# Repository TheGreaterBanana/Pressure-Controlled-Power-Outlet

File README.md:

# Pressure-Controlled-Power-Outlet
This is my (for sure) late Birthday present for my mom:

The idea for this project is that she have a water bin that holds water off of the roof of her house. Which my mother uses to water her gardens. The problem is that the pump she uses does not stop when the pressure starts to build!

So this is ment to fix this by using a water pressure sensor to see when the hose nozzel is closed by detecting a large jump in pressure then disablling the outlet that is powering the pump. Then when the nozzel is opened again this will detect the drop in pressure and re-enable the outlet.

This respository will have the code for the pico (RP2040) microcontroller, the schematics for the PCB and the case that will be used. 

The design philosophy for this project is to have everything as simple and cheap as possible, for this as many components as possible will be through hole as I dont want to pay to have parts placed on the pcb. If a part has to be surface mount it will have a extra large footprint to make it as easy as possible to assemble.

The specs:
    - 125V
    - 20A
    - GFCI protected outlets
    - Useable outdoors

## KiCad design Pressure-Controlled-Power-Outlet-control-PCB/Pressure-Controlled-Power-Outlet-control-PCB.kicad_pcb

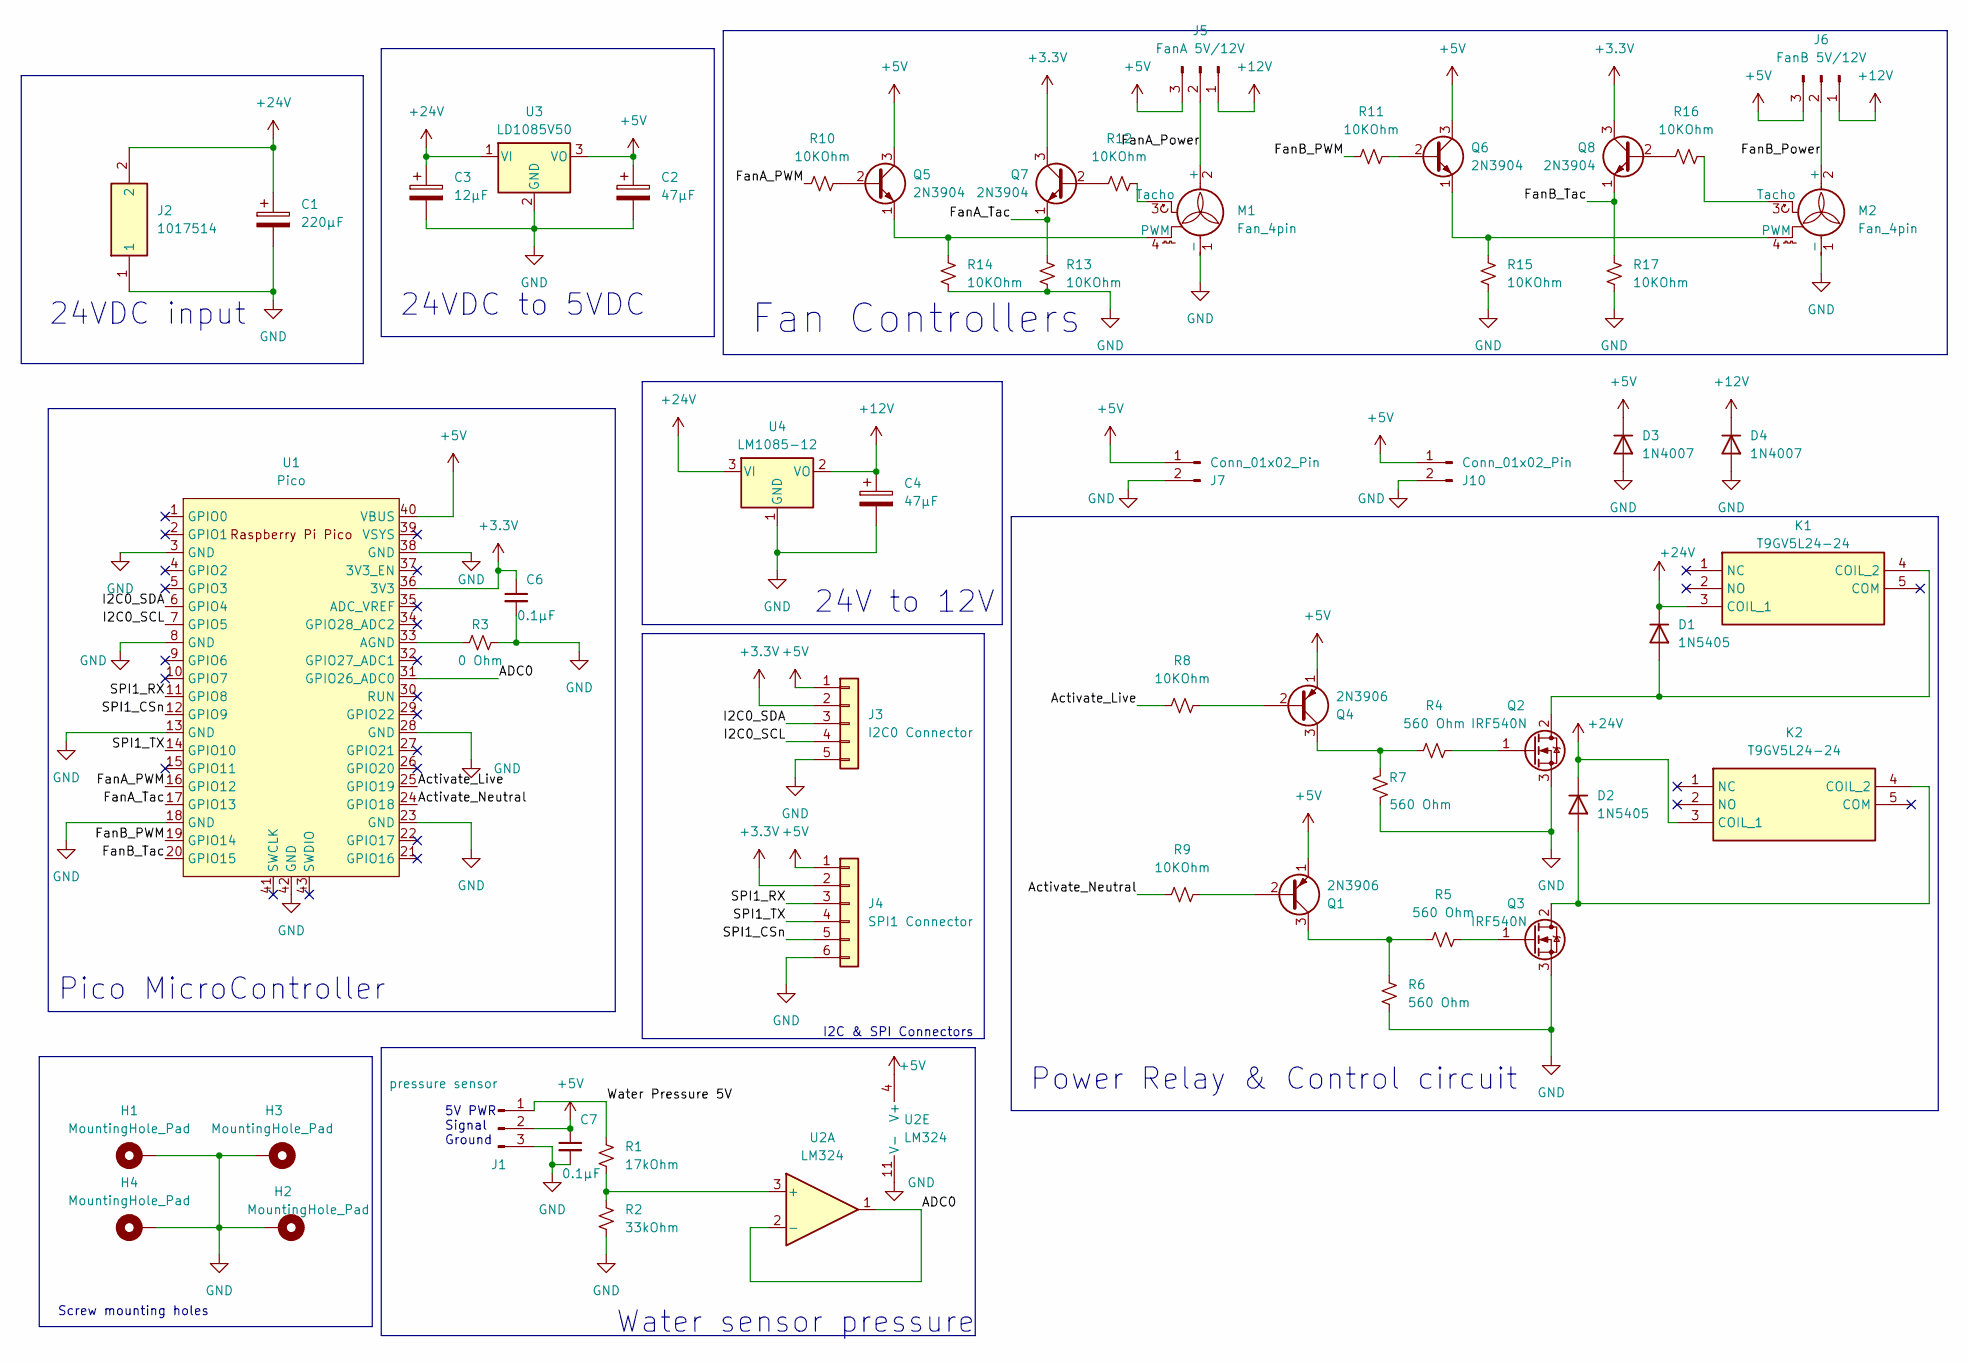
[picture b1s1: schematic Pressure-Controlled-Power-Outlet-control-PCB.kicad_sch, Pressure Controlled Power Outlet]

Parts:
C1: 220µF; CP_Radial_D10.0mm_P5.00mm
C2, C4: 47µF; CP_Radial_D10.0mm_P5.00mm
C3: 12µF; CP_Radial_D10.0mm_P5.00mm
C6, C7: 0.1µF; C_Rect_L7.2mm_W2.5mm_P5.00mm_FKS2_FKP2_MKS2_MKP2
D1, D2: 1N5405; D_DO-201AD_P15.24mm_Horizontal
D3, D4: 1N4007; D_DO-41_SOD81_P10.16mm_Horizontal
H1, H2, H3, H4: MountingHole_Pad; MountingHole_3.2mm_M3_ISO7380_Pad
J1: pressure sensor; PinHeader_1x03_P2.54mm_Vertical
J2: 1017514; Mouser Part Number 651-1017514
J3: I2C0 Connector; PinHeader_1x05_P2.54mm_Vertical
J4: SPI1 Connector; PinHeader_1x06_P2.54mm_Vertical
J5: FanA 5V/12V; PinHeader_1x03_P2.54mm_Vertical
J6: FanB 5V/12V; PinHeader_1x03_P2.54mm_Vertical
J7: Conn_01x02_Pin; JST_EH_B2B-EH-A_1x02_P2.50mm_Vertical
J10: Conn_01x02_Pin; PinHeader_1x02_P2.54mm_Vertical
K1, K2: T9GV5L24-24; T9GV5L2424; Mouser Part Number 655-T9GV5L24-24
M1, M2: Fan_4pin; FanPinHeader_1x04_P2.54mm_Vertical
Q1, Q4: 2N3906; TO-92_Inline
Q2, Q3: IRF540N; TO-220-3_Vertical
Q5, Q6, Q7, Q8: 2N3904; TO-92_Inline
R1: 17kOhm; R_Axial_DIN0207_L6.3mm_D2.5mm_P2.54mm_Vertical
R2: 33kOhm; R_Axial_DIN0207_L6.3mm_D2.5mm_P2.54mm_Vertical
R3: 0 Ohm; R_Axial_DIN0207_L6.3mm_D2.5mm_P2.54mm_Vertical
R4, R5, R6, R7: 560 Ohm; R_Axial_DIN0207_L6.3mm_D2.5mm_P2.54mm_Vertical
R8, R9, R10, R11, R12, R13, R14, R15, R16, R17: 10KOhm; R_Axial_DIN0207_L6.3mm_D2.5mm_P2.54mm_Vertical
U1: Pico; RPi_Pico_SMD_TH
U2: LM324
U3: LD1085V50; TO-220-3_Vertical
U4: LM1085-12; TO-220-3_Vertical

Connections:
+3.3V: C6.1, J3.2, J4.2, Q7.3 (C), Q8.3 (C), U1.36 (3V3)
+5V: C2.1, C7.1, D3.1 (K), J1.2, J3.1, J4.1, J5.3, J6.3, J7.1, J10.1, Q1.1 (E), Q4.1 (E), Q5.3 (C), Q6.3 (C), U1.40 (VBUS), U2.4 (V+), U3.3 (VO)
+12V: C4.1, D4.1 (K), J5.1, J6.1, U4.2 (VO)
+24V: C1.1, C3.1, D1.1 (K), D2.1 (K), J2.2, K1.3 (COIL_1), K2.3 (COIL_1), U3.1 (VI), U4.3 (VI)
/ADC0: U1.31 (GPIO26_ADC0), U2.1, U2.2 (-)
/Activate_Live: R8.1, U1.25 (GPIO19)
/Activate_Neutral: R9.1, U1.24 (GPIO18)
/FanA_PWM: R10.1, U1.16 (GPIO12)
/FanA_Power: J5.2, M1.2 (+)
/FanA_Tac: Q7.1 (E), R13.2, U1.17 (GPIO13)
/FanB_PWM: R11.1, U1.19 (GPIO14)
/FanB_Power: J6.2, M2.2 (+)
/FanB_Tac: Q8.1 (E), R17.2, U1.20 (GPIO15)
/I2C0_SCL: J3.4, U1.7 (GPIO5)
/I2C0_SDA: J3.3, U1.6 (GPIO4)
/SPI1_CSn: J4.5, U1.12 (GPIO9)
/SPI1_RX: J4.3, U1.11 (GPIO8)
/SPI1_TX: J4.4, U1.14 (GPIO10)
/Water Pressure 5V: J1.1, R1.2
GND: C1.2, C2.2, C3.2, C4.2, C6.2, C7.2, D3.2 (A), D4.2 (A), H1.1, H2.1, H3.1, H4.1, J1.3, J2.1, J3.5, J4.6, J7.2, J10.2, M1.1 (-), M2.1 (-), Q2.3 (S), Q3.3 (S), R2.2, R3.2, R6.1, R7.1, R13.1, R14.1, R15.1, R17.1, U1.3 (GND), U1.8 (GND), U1.13 (GND), U1.18 (GND), U1.23 (GND), U1.28 (GND), U1.38 (GND), U1.42 (GND), U2.11 (V-), U3.2 (GND), U4.1 (GND)
unnamed: D1.2 (A), K1.4 (COIL_2), Q2.2 (D)
unnamed: D2.2 (A), K2.4 (COIL_2), Q3.2 (D)
unnamed: M1.4 (PWM), Q5.1 (E), R14.2
unnamed: M1.3 (Tacho), R12.2
unnamed: M2.4 (PWM), Q6.1 (E), R15.2
unnamed: M2.3 (Tacho), R16.2
unnamed: Q1.2 (B), R9.2
unnamed: Q1.3 (C), R5.1, R6.2
unnamed: Q2.1 (G), R4.2
unnamed: Q3.1 (G), R5.2
unnamed: Q4.2 (B), R8.2
unnamed: Q4.3 (C), R4.1, R7.2
unnamed: Q5.2 (B), R10.2
unnamed: Q6.2 (B), R11.2
unnamed: Q7.2 (B), R12.1
unnamed: Q8.2 (B), R16.1
unnamed: R3.1, U1.33 (AGND)
unnamed: R1.1, R2.1, U2.3 (+)

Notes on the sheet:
Screw mounting holes
24VDC input
24V to 12V
Power Relay & Control circuit
5V PWR Signal Ground
Pico MicroController
Fan Controllers
I2C & SPI Connectors
24VDC to 5VDC
Water sensor pressure

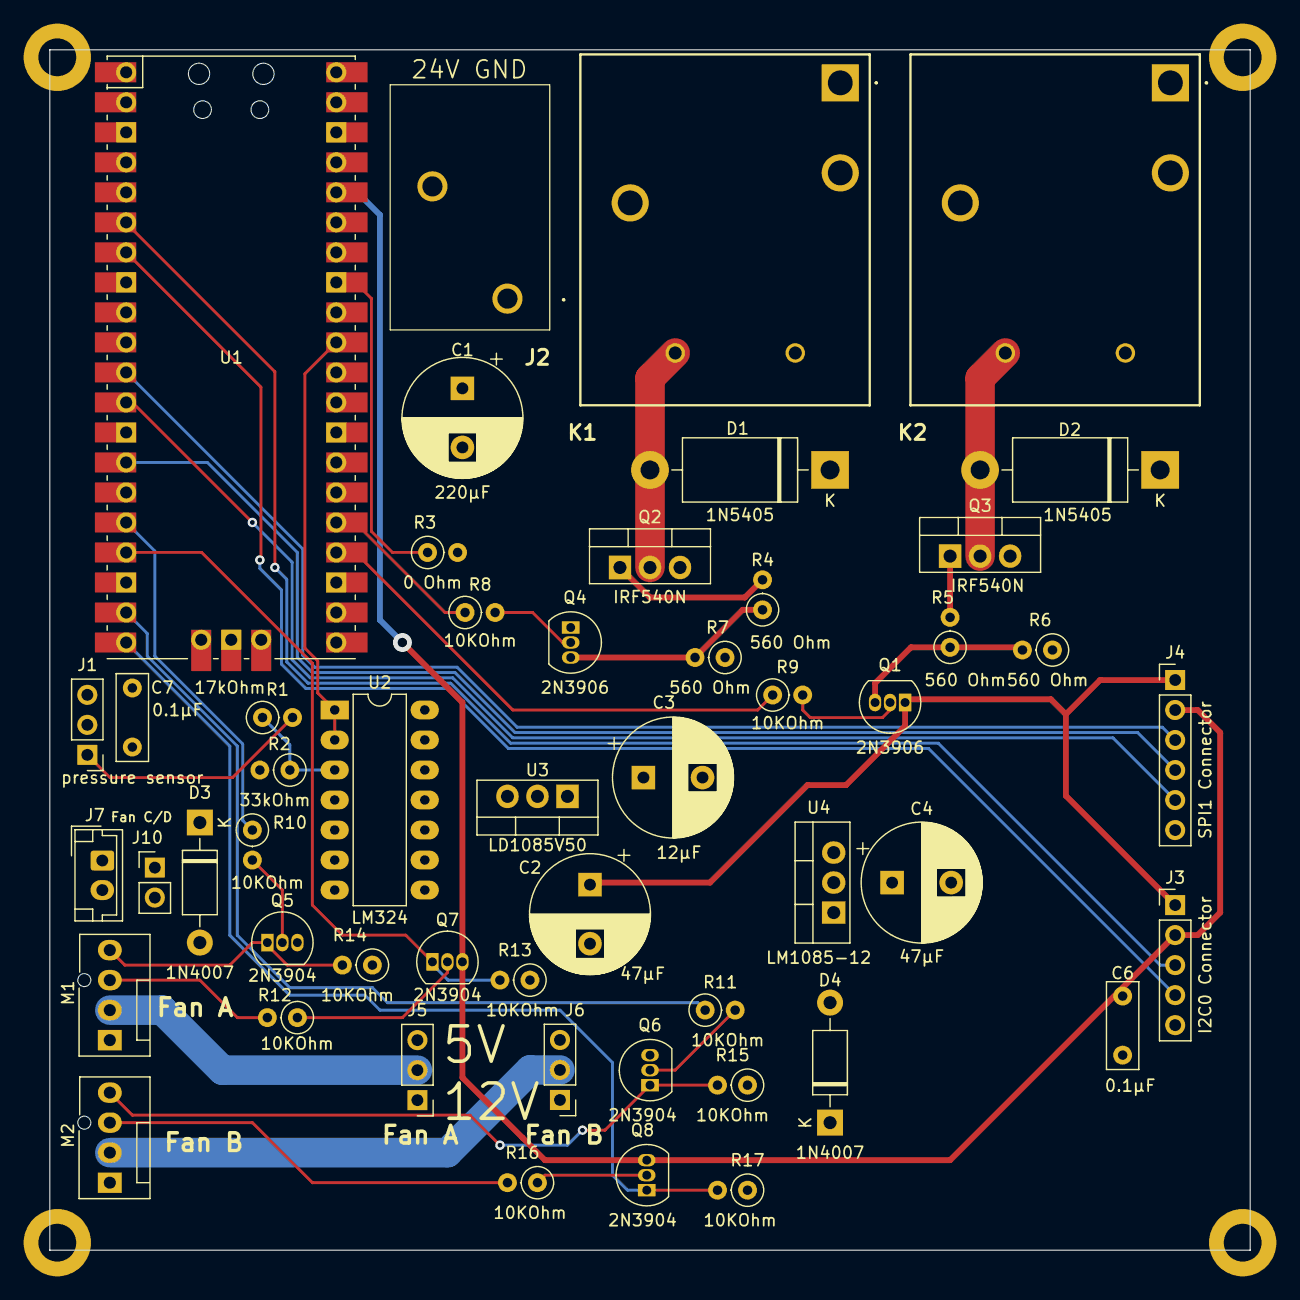
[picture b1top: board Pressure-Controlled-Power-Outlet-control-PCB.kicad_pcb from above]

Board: 4 copper layers, 101.6 x 101.6 mm, 55 parts (0 on the bottom side), 38 nets.

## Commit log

2024-07-17 added ReadMe File
2024-07-17 added some of the part list
2024-07-17 added control board KiCAD
2024-07-17 added pico model from https://github.com/ncarandini/KiCad-RP-Pico
2024-07-17 Creating a 5V analog to 3.3V analog converter for SEN0257
2024-07-18 created a 5v logic to 3.3v logic for the water sensor
2024-07-18 have most of the traces ran on pcb but controlling the relays
2024-07-18 removed onboard power supply and replaced it with an external 24V PSU, and removed High voltage pcb connections as relays have connectors on the top of them
2024-07-18 wired PCB but the footprint does not match the relay im using so i need to swap the relay :(
2024-07-18 added new relays
2024-07-18 fixed PCB
2024-07-19 should be done need to review the board to ensure everything is good
2024-07-19 updated parts list with latest parts
2024-07-19 removed grb files that where in the wrong spot
2024-07-19 updated to use the sen0257 WPS
2024-07-19 fixed PCB design to allow for better spacing of parts
2024-07-19 added a spi & I2C connector incase someone wants to add more sensors to the board
2024-07-19 forgor to save
2024-07-19 updated gbr files
2024-07-20 end of day save
2024-07-20 sign a new feature creep added two fan headers that can power ether 24 or 5 volt fans
2024-07-20 Added name
2024-07-20 hopefully final push for the day
2024-07-20 hopefully final rev for the night
2024-07-20 added name to pcb
2024-07-20 done for the day fixed some part spacing and traces
2024-07-20 redid the fan controllers
2024-07-20 welp moved some stuff around
2024-07-20 upgraded diodes to 1n5405 from 1n5401
2024-07-20 finished the through hole version of the board going to make a smd version for pick and place
2024-07-20 added a copy that will be mostly surface mount components
2024-07-20 make a quick version that has some SMD for pick and place
2024-07-21 added better longer lasting caps
2024-07-21 hopefully done this PCB
2024-07-21 updated 220µF cap
2024-07-21 updated parts list
2024-07-21 changed 24V fan power to 12V
2024-07-21 added 5v fan headers
2024-07-21 added some basic diodes to protect from fan feedback
2024-07-21 added some power filter caps
2024-07-21 :confounded: what is the pcb
2024-07-21 some autosave
2024-07-21 moved some traces and components
2024-07-22 created basic script that can read the values out of the pressure sensor
2024-07-23 created new greber files
2024-07-25 made a simple version of the pcb that does not have a microcontroller
2024-07-25 old pcb design
2024-07-25 created new updated PCB design that will fit the mount of the case
2024-07-25 updated pcb to version 1.5.25
2024-07-25 hope im done the pcb
2024-07-26 moved some components around on the PCB
2024-07-26 move smd and simple versions to a tangents folder
2024-07-26 added label to the PWR in to show the 24V and GND sides
2024-07-28 moved some componets
2024-07-29 updated gerber
